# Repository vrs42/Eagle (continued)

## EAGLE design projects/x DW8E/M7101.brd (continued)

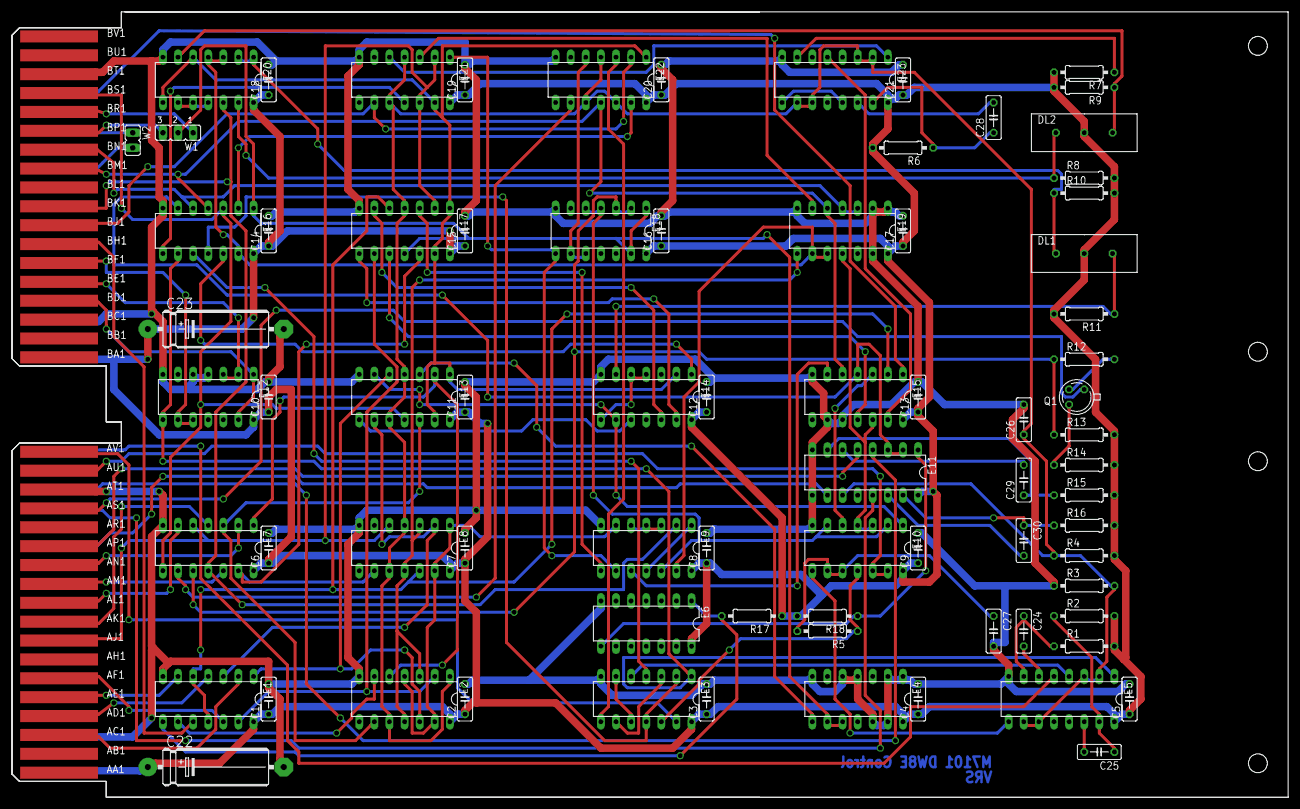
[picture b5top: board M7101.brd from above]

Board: 2 copper layers, 214.6 x 132.1 mm, 78 parts (0 on the bottom side), 103 nets.

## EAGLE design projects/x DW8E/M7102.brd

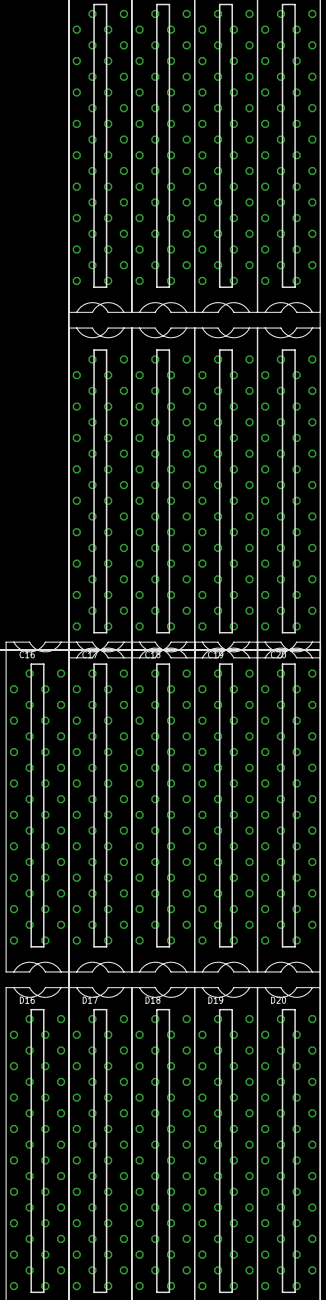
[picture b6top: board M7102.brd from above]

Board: 2 copper layers, 25 parts (0 on the bottom side), 3 nets, no tracks yet.

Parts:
AB17, AB18, AB19, AB20: M7102; H807-2
C16, C17, C18, C19, C20: M903; H807
D16, D17, D18, D19, D20: M903; H807
U$1, U$2, U$3, U$4, U$6, U$7, U$8, U$9, U$10, U$11, U$12: CBLOCK

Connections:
-15V: AB17.AB2, AB17.BB2, AB18.AB2, AB18.BB2, AB19.AB2, AB19.BB2, AB20.AB2, AB20.BB2
GND: AB17.AC2, AB17.AT1, AB17.BC2, AB17.BT1, AB18.AC2, AB18.AT1, AB18.BC2, AB18.BT1, AB19.AC2, AB19.AT1, AB19.BC2, AB19.BT1, AB20.AC2, AB20.AT1, AB20.BC2, AB20.BT1, C16.A1, C16.C1, C16.C2, C16.F1, C16.F2, C16.J2, C16.K1, C16.L2, C16.N1, C16.N2, C16.R1, C16.R2, C16.T1, C16.U2, C17.A1, C17.C1, C17.C2, C17.F1, C17.F2, C17.J2, C17.K1, C17.L2, C17.N1, C17.N2, C17.R1, C17.R2, C17.T1, C17.U2, C18.A1, C18.C1, C18.C2, C18.F1, C18.F2, C18.J2, C18.K1, C18.L2, C18.N1, C18.N2, C18.R1, C18.R2, C18.T1, C18.U2, C19.A1, C19.C1, C19.C2, C19.F1, C19.F2, C19.J2, C19.K1, C19.L2, C19.N1, C19.N2, C19.R1, C19.R2, C19.T1, C19.U2, C20.A1, C20.C1, C20.C2, C20.F1, C20.F2, C20.J2, C20.K1, C20.L2, C20.N1, C20.N2, C20.R1, C20.R2, C20.T1, C20.U2, D16.A1, D16.C1, D16.C2, D16.F1, D16.F2, D16.J2, D16.K1, D16.L2, D16.N1, D16.N2, D16.R1, D16.R2, D16.T1, D16.U2, D17.A1, D17.C1, D17.C2, D17.F1, D17.F2, D17.J2, D17.K1, D17.L2, D17.N1, D17.N2, D17.R1, D17.R2, D17.T1, D17.U2, D18.A1, D18.C1, D18.C2, D18.F1, D18.F2, D18.J2, D18.K1, D18.L2, D18.N1, D18.N2, D18.R1, D18.R2, D18.T1, D18.U2, D19.A1, D19.C1, D19.C2, D19.F1, D19.F2, D19.J2, D19.K1, D19.L2, D19.N1, D19.N2, D19.R1, D19.R2, D19.T1, D19.U2, D20.A1, D20.C1, D20.C2, D20.F1, D20.F2, D20.J2, D20.K1, D20.L2, D20.N1, D20.N2, D20.R1, D20.R2, D20.T1, D20.U2
VCC: AB17.AA2, AB17.BA2, AB18.AA2, AB18.BA2, AB19.AA2, AB19.BA2, AB20.AA2, AB20.BA2
